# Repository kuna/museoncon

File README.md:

Muse-on Controller
==================

A revival of muse-on controller to a fully functional IIDX gamepad with LED equipped.

Composed of:
* Model (top board)
* Firmware (RP2350)
* Circuit
* Configurator (web page)

## Demo

## Model preview

## Circuit preview

## Configurator

`configurator/index.html` changes the output mode and shows live input:
buttons before and after debounce, turntable position, sensor levels, and
invalid quadrature steps.

Pick the gamepad mode for the game, since each game reads the turntable
differently:

| Game | Mode |
|---|---|
| beatoraja (analog scratch off, the default) | GAMEPAD · beatoraja |
| LR2 | GAMEPAD · LR2 |
| INFINITAS, or beatoraja with analog scratch on | GAMEPAD · INFINITAS |

Open the file directly in Chrome or Edge on a desktop (Web Serial is not
available in Firefox or Safari), plug in the controller, and press Connect.
No server or install is needed. The protocol is documented in
[firmware/README.md](firmware/README.md#configurator-port).

With several controllers plugged in, the page connects to the first free
one. To pick another, press Disconnect, then Connect and choose its port.
The browser lists ports only by name (e.g. `COM5`), so press "Blink LEDs"
to see which controller you got. Each tab holds one controller, so you can
also open one tab per controller.

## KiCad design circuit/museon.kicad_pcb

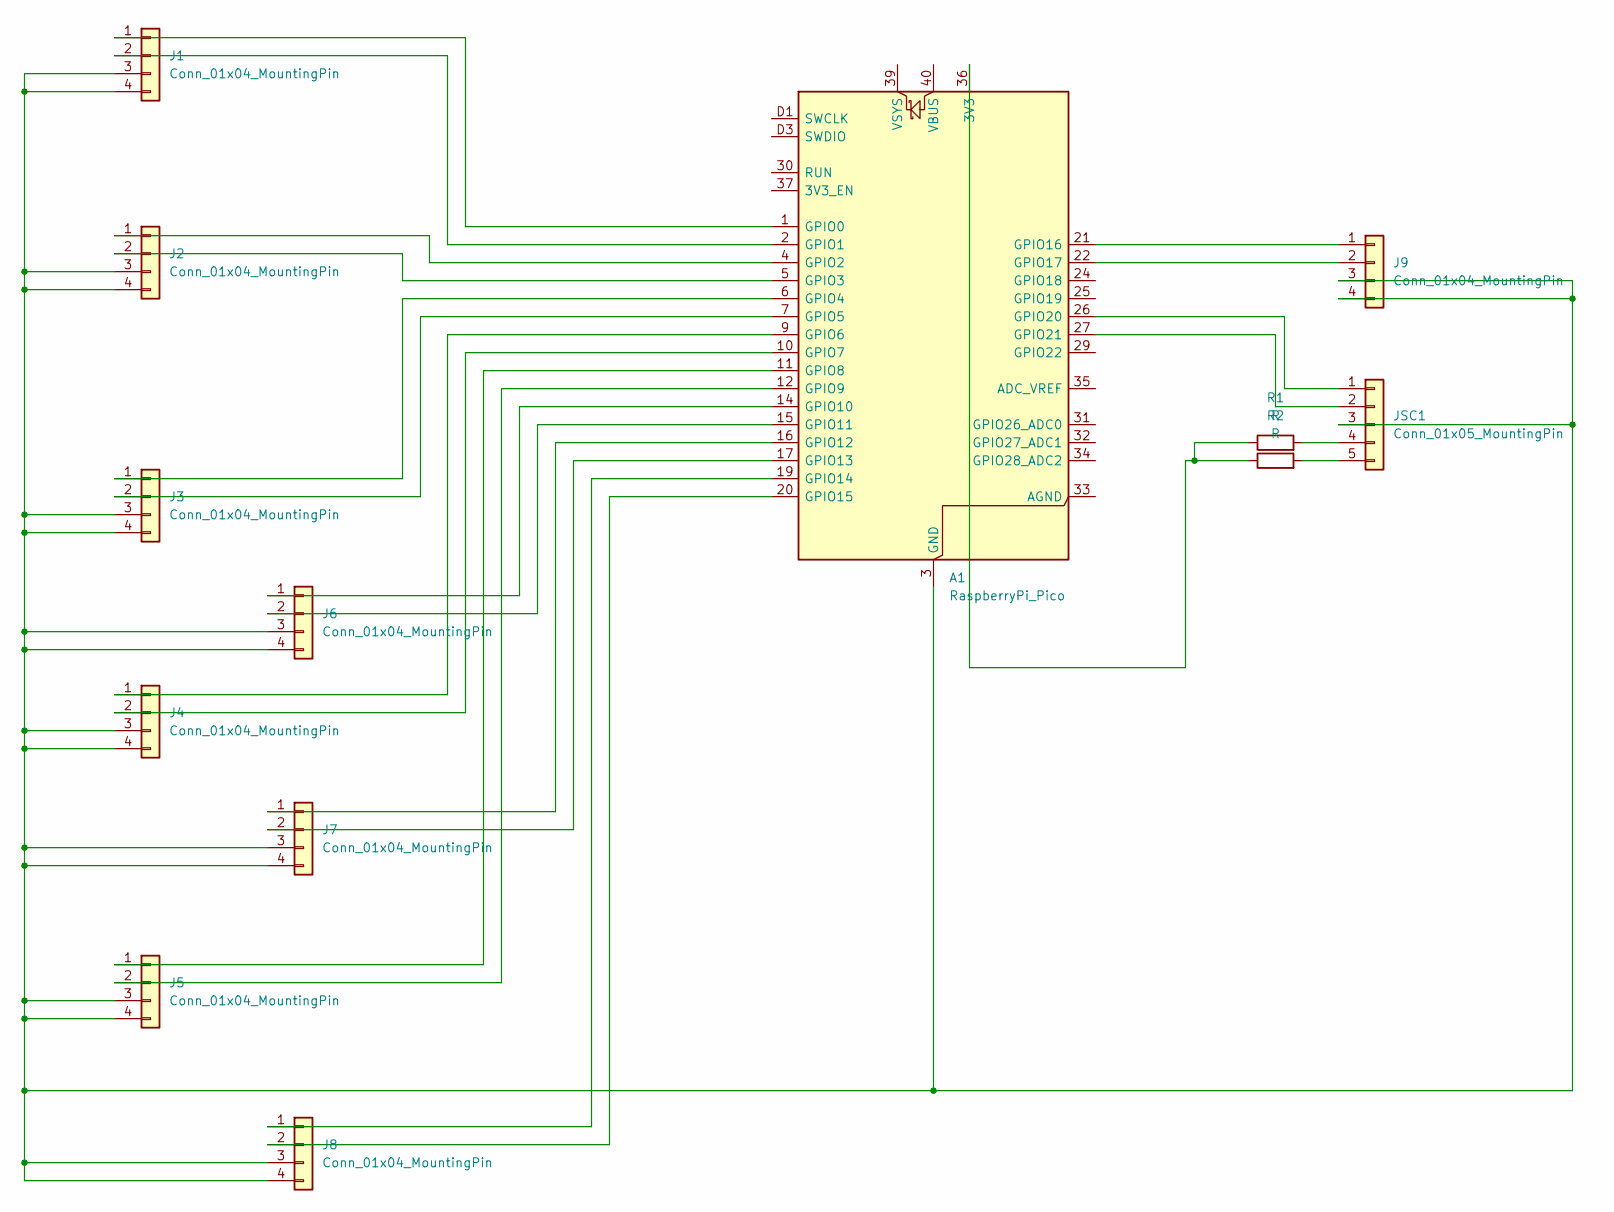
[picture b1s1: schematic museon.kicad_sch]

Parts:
A1: RaspberryPi_Pico; RaspberryPi_Pico_SMD_HandSolder
J1, J2, J3, J4, J5, J6, J7, J8, J9: Conn_01x04_MountingPin; JST_XH_B4B-XH-A_1x04_P2.50mm_Vertical
JSC1: Conn_01x05_MountingPin; JST_XH_B5B-XH-A_1x05_P2.50mm_Vertical
R1, R2: R; R_Axial_DIN0207_L6.3mm_D2.5mm_P7.62mm_Horizontal

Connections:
unnamed: A1.36 (3V3), R1.1, R2.1
unnamed: A1.1 (GPIO0), J1.1
unnamed: A1.2 (GPIO1), J1.2
unnamed: A1.4 (GPIO2), J2.1
unnamed: A1.5 (GPIO3), J2.2
unnamed: A1.6 (GPIO4), J3.1
unnamed: A1.7 (GPIO5), J3.2
unnamed: A1.9 (GPIO6), J4.1
unnamed: A1.10 (GPIO7), J4.2
unnamed: A1.11 (GPIO8), J5.1
unnamed: A1.12 (GPIO9), J5.2
unnamed: A1.14 (GPIO10), J6.1
unnamed: A1.15 (GPIO11), J6.2
unnamed: A1.16 (GPIO12), J7.1
unnamed: A1.17 (GPIO13), J7.2
unnamed: A1.19 (GPIO14), J8.1
unnamed: A1.20 (GPIO15), J8.2
unnamed: A1.21 (GPIO16), J9.1
unnamed: A1.22 (GPIO17), J9.2
unnamed: A1.26 (GPIO20), JSC1.1
unnamed: A1.27 (GPIO21), JSC1.2
unnamed: A1.3 (GND), A1.8 (GND), A1.13 (GND), A1.18 (GND), A1.23 (GND), A1.28 (GND), A1.38 (GND), A1.D2 (GND), J1.3, J1.4, J2.3, J2.4, J3.3, J3.4, J4.3, J4.4, J5.3, J5.4, J6.3, J6.4, J7.3, J7.4, J8.3, J8.4, J9.3, J9.4, JSC1.3
unnamed: JSC1.4, R1.2
unnamed: JSC1.5, R2.2

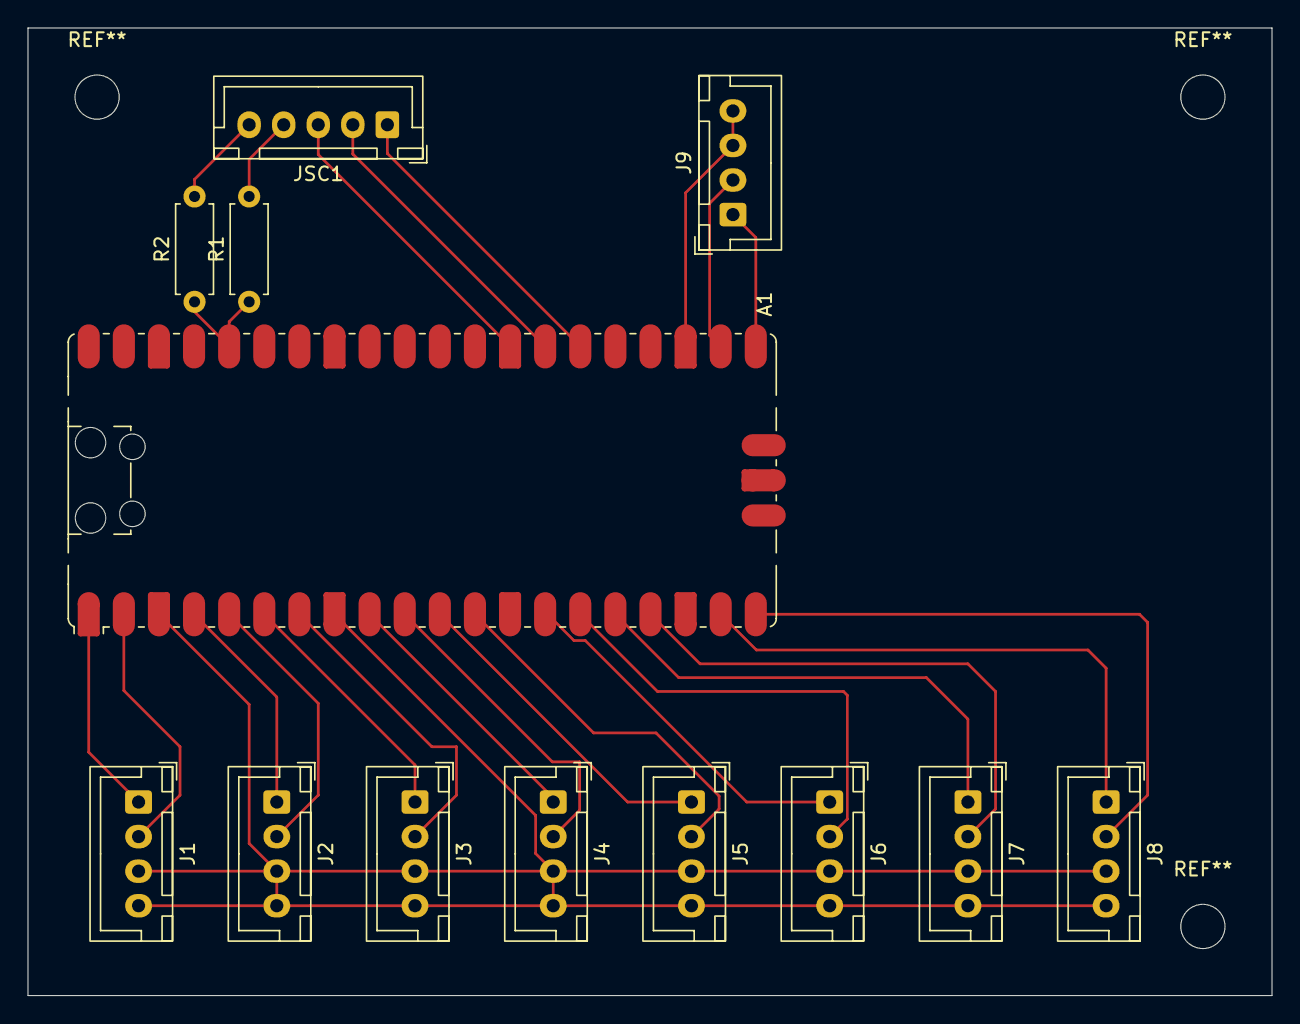
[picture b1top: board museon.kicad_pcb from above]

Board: 2 copper layers, 90.0 x 70.0 mm, 13 parts (0 on the bottom side), 24 nets.
